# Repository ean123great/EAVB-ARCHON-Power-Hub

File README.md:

# EAVB ARCHON 15W Power Hub
**High-Efficiency DC-DC Step-Down Architecture with PMOS Protection**

Designed by **Elcyn Andrew V. Booc** | EAVB Electronics

The **ARCHON Power Hub** is a compact, industrial-grade power management module designed for autonomous robotics, IoT systems, and high-reliability embedded environments. Utilizing a 1.5 MHz switching frequency and the proprietary "Ocean Ground Strategy," ARCHON delivers up to 15W of continuous power with exceptional thermal stability and minimal EMI.

---

### Key Architectural Features
* **Zero-Drop Reverse Polarity Protection:** Utilizes an AO4407A P-Channel MOSFET instead of a standard Schottky diode, eliminating thermal dissipation and voltage drop at the input stage.
* **The "Ocean Ground Strategy":** A highly optimized SMD PCB layout utilizing extensive ground pours and thermal via stitching to turn the entire FR4 board into a passive heatsink.
* **High-Frequency Regulation:** Driven by the MP1584EN switching regulator operating at 1.5 MHz, allowing for extreme component density and rapid transient response.
* **Industrial Form Factor:** Exclusively utilizes Surface Mount Devices (SMD), including 0805 passives and SOIC-8 packaging, for a manufacturing-ready footprint.

---

### Absolute Maximum Ratings & Specifications

| Parameter | Specification | Notes |
| :--- | :--- | :--- |
| **Input Voltage Range** | 4.5V to 28V DC | Regulated |
| **Output Voltage** | 5.0V (Adjustable) | Tuned via precision resistor network |
| **Max Continuous Current** | 3A | Requires adequate airflow at max load |
| **Maximum Power Output** | 15W | |
| **Peak Efficiency ($\eta$)** | Up to 92% | Load dependent |
| **Switching Frequency** | 1.5 MHz | Reduces inductor size requirement |

---

### Repository Structure
* `/Hardware` - KiCad schematic (`.kicad_sch`), PCB layout (`.kicad_pcb`), and manufacturing Gerber files.
* `/Docs` - Official EAVB technical specifications, absolute maximum ratings, and theory of operation (PDF).

---

### Intellectual Property & Commercial Licensing
This hardware design is protected under the **CC BY-NC-SA 4.0** license. 
* **Non-Commercial Use:** Students, hobbyists, and researchers are free to study, build, and modify this architecture for personal or academic use, provided credit is given to **EAVB Electronics**.
* **Commercial Use:** Manufacturing this board for sale or integrating this architecture into a commercial product is strictly prohibited under this license.

> **For Commercial Manufacturing Rights:** > Please contact the Lead Architect at **eavb.electronics@gmail.com** for corporate licensing agreements.

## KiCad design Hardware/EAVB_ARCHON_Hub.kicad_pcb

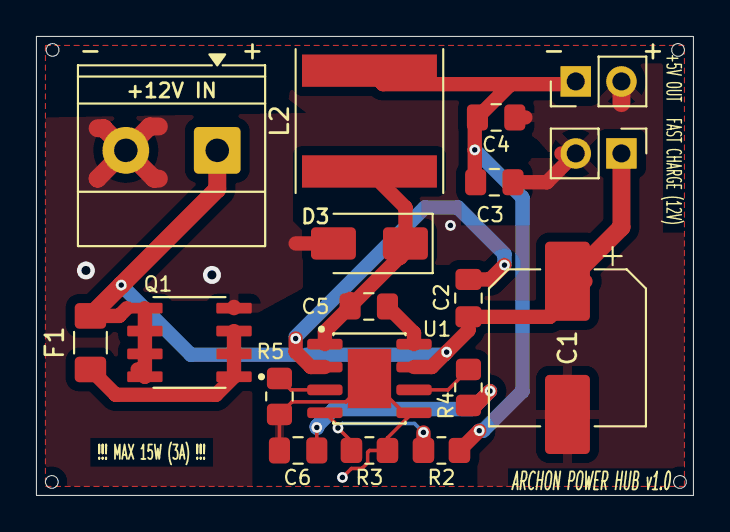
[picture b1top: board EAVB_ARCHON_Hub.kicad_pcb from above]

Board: 2 copper layers, 36.5 x 25.5 mm, 18 parts (0 on the bottom side), 11 nets.

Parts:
+5V OUT: Conn_01x02_Pin; PinHeader_1x02_P2.54mm_Vertical
+12V IN: Screw_Terminal_01x02; TerminalBlock_Phoenix_MKDS-1,5-2-5.08_1x02_P5.08mm_Horizont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
C1: C_Polarized; CP_Elec_8x10.5
C2, C3, C4, C5, C6: C; C_0805_2012Metric_Pad1.18x1.45mm_HandSolder
D3: D_Schottky; D_SMA
F1: Fuse; Fuse_1206_3216Metric_Pad1.42x1.75mm_HandSolder
FAST CHARGE (12V): Type-C_Module_Power; PinHeader_1x02_P2.54mm_Vertical
L2: L; L_Taiyo-Yuden_NR-80xx
Q1: Q_PMOS_DGS; SOIC127P600X175-8N
R2, R3, R4, R5: R; R_0805_2012Metric_Pad1.20x1.40mm_HandSolder
U1: MP1584EN; SOIC127P600X170-9N

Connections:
+5V: +5V OUT.1, C3.1, C4.1, L2.2, R2.2
+12V: +12V IN.1, C1.1, C2.1, F1.2, FAST CHARGE (12V).1, Q1.5, Q1.6, Q1.7, Q1.8, U1.7 (VIN)
GND: +5V OUT.2, +12V IN.2, C1.2, C3.2, C4.2, C6.2, D3.2 (A), FAST CHARGE (12V).2, Q1.4, R3.2, R5.1, U1.5 (GND), U1.9 (GND)
unnamed: C6.1, R4.1
unnamed: C5.1, D3.1 (K), L2.1, U1.1 (SW)
unnamed: F1.1, Q1.1, Q1.2, Q1.3
unnamed: C5.2, U1.8 (BST)
unnamed: R5.2, U1.3 (COMP)
unnamed: C2.2, U1.2 (EN)
unnamed: R2.1, R3.1, U1.4 (FB)
unnamed: R4.2, U1.6 (FREQ)

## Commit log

2026-03-21 Rename EAVB_ARCHON_Hub_v1.0.kicad_sch to EAVB_ARCHON_Hub.kicad_sch
2026-03-21 Rename EAVB_ARCHON_Hub_v1.0.kicad_pro to EAVB_ARCHON_Hub.kicad_pro
2026-03-21 Rename EAVB_ARCHON_Hub_v1.0.kicad_pcb to EAVB_ARCHON_Hub.kicad_pcb
2026-03-21 Rename EAVB_ARCHON_15W_Datasheet_v1.0.pdf to EAVB_ARCHON_Documentation.pdf
